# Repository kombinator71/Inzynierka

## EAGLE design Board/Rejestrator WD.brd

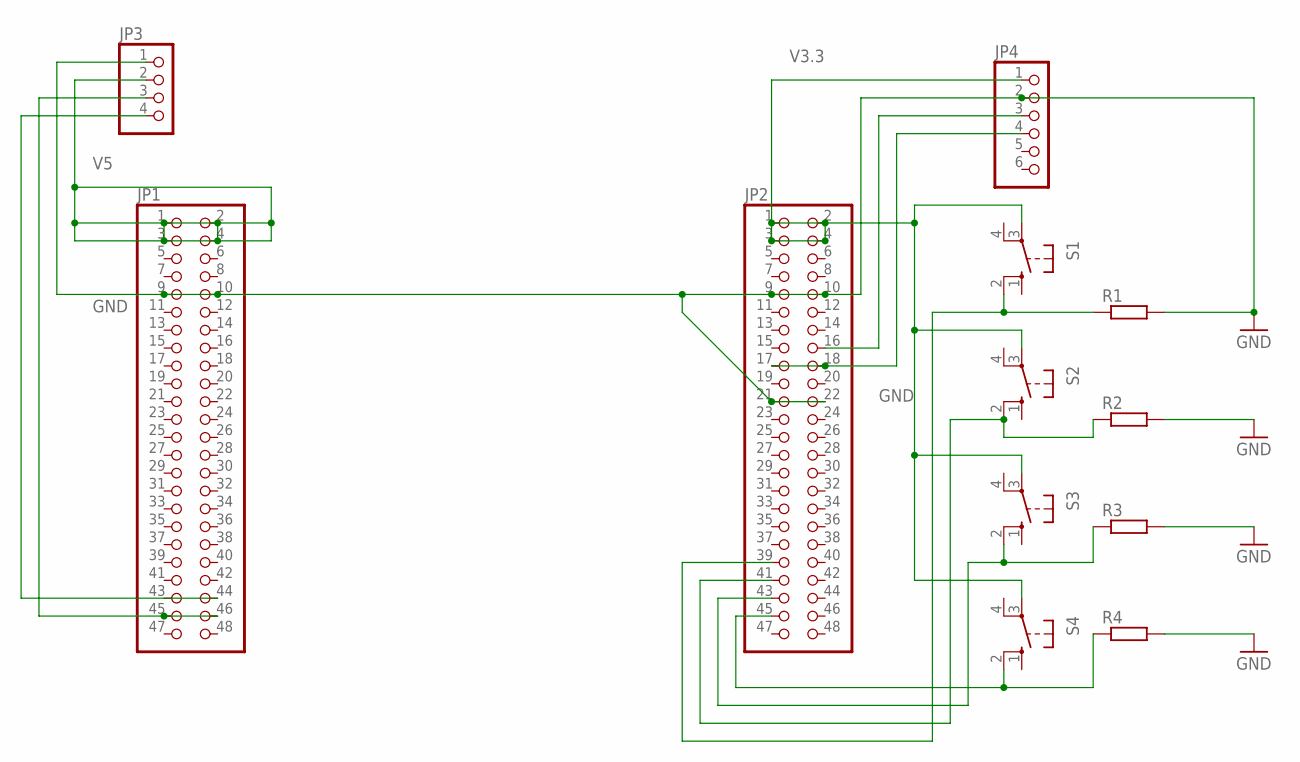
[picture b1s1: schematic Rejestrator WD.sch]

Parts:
JP1, JP2: PINHD-2X24; 2X24
JP3: PINHD-1X4/90; 1X04/90
JP4: PINHD-1X6; 1X06
R1, R2, R3, R4: R-EU_0207/10; 0207/10
S1, S2, S3, S4: 40-XX; B3F-40XX

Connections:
GND: JP1.9, JP1.10, JP2.9, JP2.10, JP2.21, JP2.22, JP3.1, JP4.2, R1.2, R2.2, R3.2, R4.2
unnamed: JP1.45, JP1.46, JP3.3
unnamed: JP2.16, JP4.3
unnamed: JP1.44, JP3.4
unnamed: JP2.45, R4.1, S4.2 (S1)
unnamed: JP2.43, R3.1, S3.2 (S1)
unnamed: JP2.41, R2.1, S2.2 (S1)
unnamed: JP2.39, R1.1, S1.2 (S1)
unnamed: JP2.17, JP2.18, JP4.4
V3.3: JP2.1, JP2.2, JP2.3, JP2.4, JP4.1, S1.3, S2.3, S3.3, S4.3
V5: JP1.1, JP1.2, JP1.3, JP1.4, JP3.2

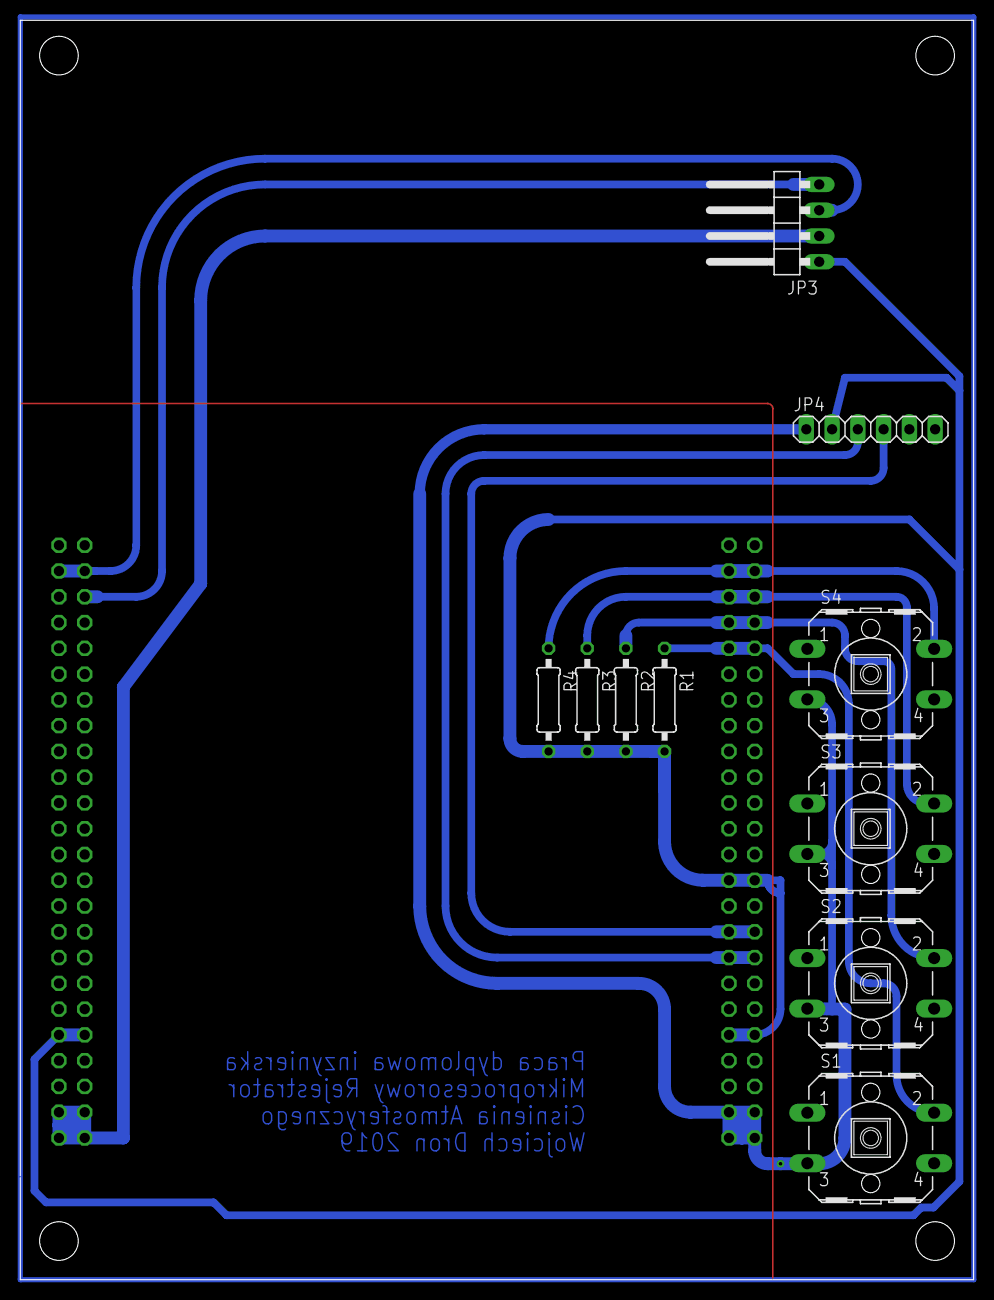
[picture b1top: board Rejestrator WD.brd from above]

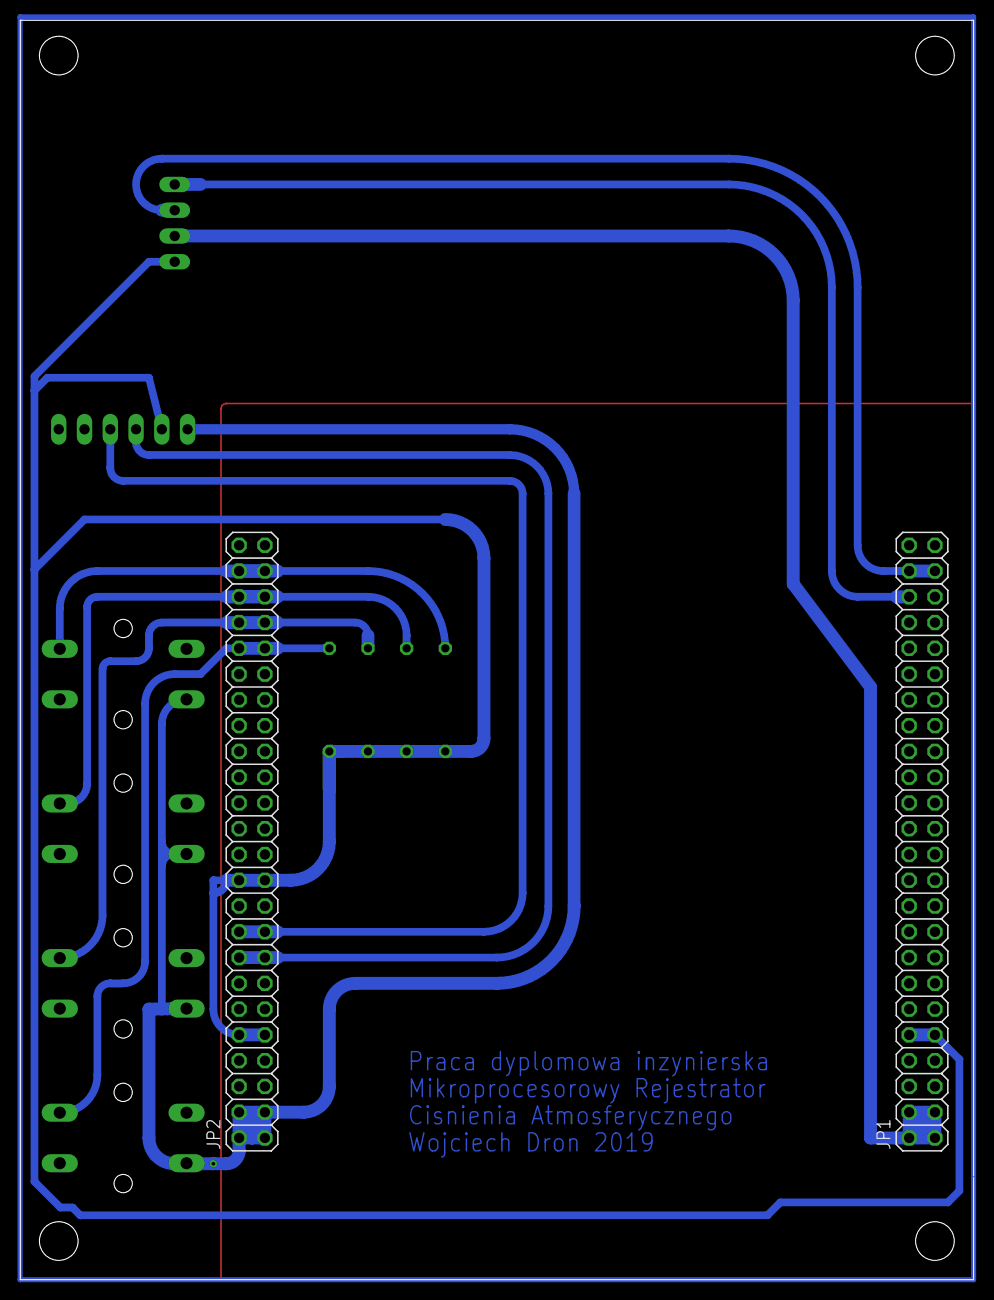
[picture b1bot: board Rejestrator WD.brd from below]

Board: 2 copper layers, 94.0 x 124.1 mm, 12 parts (2 on the bottom side), 11 nets.

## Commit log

2020-01-12 init commit
